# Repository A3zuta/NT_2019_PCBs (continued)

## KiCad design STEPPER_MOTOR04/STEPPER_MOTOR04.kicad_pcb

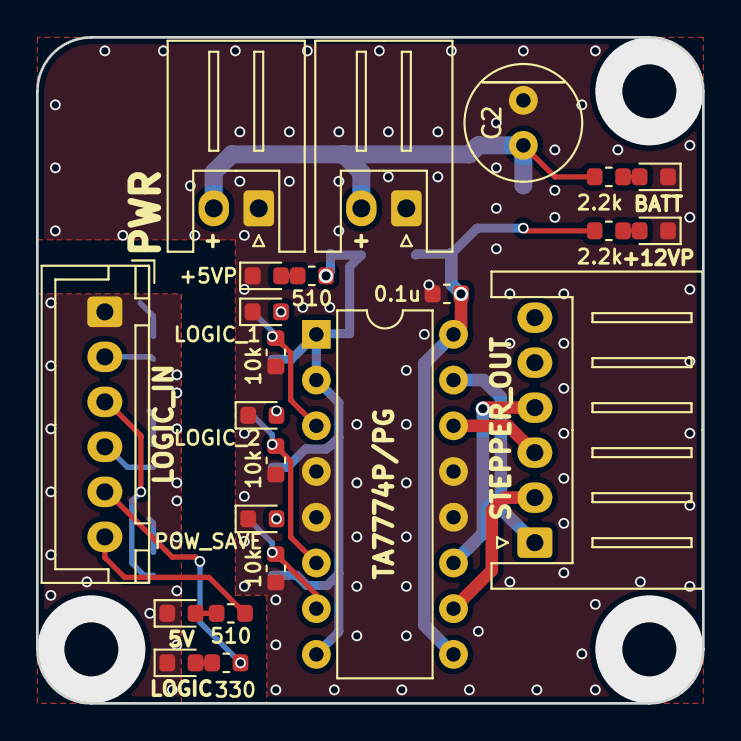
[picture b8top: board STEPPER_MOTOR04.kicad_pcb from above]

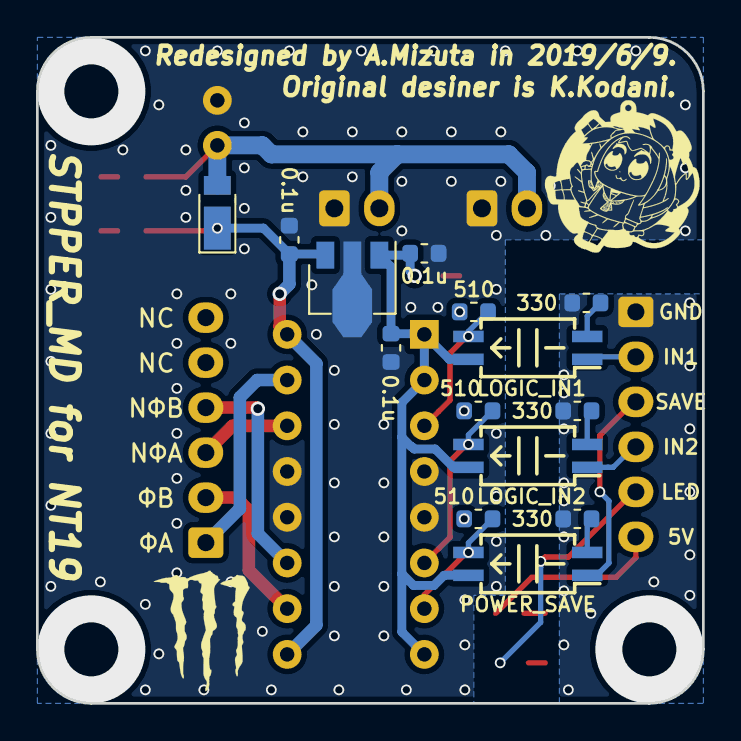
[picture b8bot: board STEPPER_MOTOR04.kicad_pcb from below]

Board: 2 copper layers, 37.0 x 37.0 mm, 37 parts (14 on the bottom side), 28 nets.

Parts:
C1, C3, C4, C5: 0.1u; C_0603_1608Metric
C2: CP; C_Radial_D6.3mm_H5.0mm_P2.50mm
D1: +5VP; LED_0603_1608Metric
D2: LOGIC; LED_0603_1608Metric
D3: +12VP; LED_0603_1608Metric
D4: DIODE_rev; D_PowerDI-123
D5: 5V; LED_0603_1608Metric
D6: BATT; LED_0603_1608Metric
D7: LOGIC_1; LED_0603_1608Metric
D8: LOGIC_2; LED_0603_1608Metric
D9: POW_SAVE; LED_0603_1608Metric
P1, P4: PWR; JST_XH_S2B-XH-A_1x02_P2.50mm_Horizontal
P2: LOGIC_IN; JST_XH_B6B-XH-A_1x06_P2.50mm_Vertical
P3: STEPPER_OUT; JST_XH_S6B-XH-A_1x06_P2.50mm_Horizontal
R1, R2, R4, R5: 330; R_0603_1608Metric
R3, R11: 2.2k; R_0603_1608Metric
R6, R7, R8: 10k; R_0603_1608Metric
R9, R10, R12, R13, R14: 510; R_0603_1608Metric
U1: TA7774P/PG; DIP-16_W7.62mm
U2: LOGIC_IN2; SOIJ-4_5.3x5.3mm_Pitch1.27mm
U3: POWER_SAVE; SOIJ-4_5.3x5.3mm_Pitch1.27mm
U4: LOGIC_IN1; SOIJ-4_5.3x5.3mm_Pitch1.27mm
U5: NJML7800; SOT-89-3

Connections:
+5V: P2.6, R10.1
+5VP: C1.1, C4.1, R9.1, U1.1, U1.2, U1.8, U2.4, U3.4, U4.4, U5.1
+12V: C3.1, C5.1, D4.1, R3.1, U1.9, U1.16, U5.3
/LD2: P2.5, R2.1
/LOGIC_IN1: P2.2, U4.1
/LOGIC_IN2: P2.4, U2.1
/LOGIC_OUT1: R8.1, R12.2, U1.3, U4.3
/LOGIC_OUT2: R6.1, R13.2, U1.6, U2.3
/NΦA_OUT: P3.3, U1.14
/NΦB_OUT: P3.4, U1.11
/POWER_SAVE: P2.3, U3.1
/POWER_SAVE_OUT: R7.1, R14.2, U1.7, U3.3
/ΦA_OUT: P3.1, U1.15
/ΦB_OUT: P3.2, U1.10
GND: D2.1, D5.1, P2.1, R1.2, R4.2, R5.2
GNDPWR: C1.2, C2.2, C3.2, C4.2, C5.2, D1.1, D3.1, D6.1, D7.1, D8.1, D9.1, P1.1, P4.1, R6.2, R7.2, R8.2, U1.4, U1.5, U1.12, U1.13, U5.2
unnamed: D1.2, R9.2
unnamed: D2.2, R2.2
unnamed: D3.2, R3.2
unnamed: D5.2, R10.2
unnamed: D6.2, R11.2
unnamed: D7.2, R12.1
unnamed: D8.2, R13.1
unnamed: D9.2, R14.1
unnamed: R1.1, U2.2
unnamed: R4.1, U3.2
unnamed: R5.1, U4.2
VSS: C2.1, D4.2, P1.2, P4.2, R11.1

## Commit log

2019-06-10 Add Power Circuit, Stepper motor driver circuit project.
2019-06-20 少しミスがあったので、直した.
2019-06-24 色々追加と修正を行った。
2019-06-26 電源基板系のものをアップロード.
2019-07-02 修正を加えた。
2019-10-08 NT金沢でのものを整理しただけ.
2019-10-10 鯖江用の基板,一応完成した(動いてくれよ)
2019-10-21 UI基板(操作盤)の完成
